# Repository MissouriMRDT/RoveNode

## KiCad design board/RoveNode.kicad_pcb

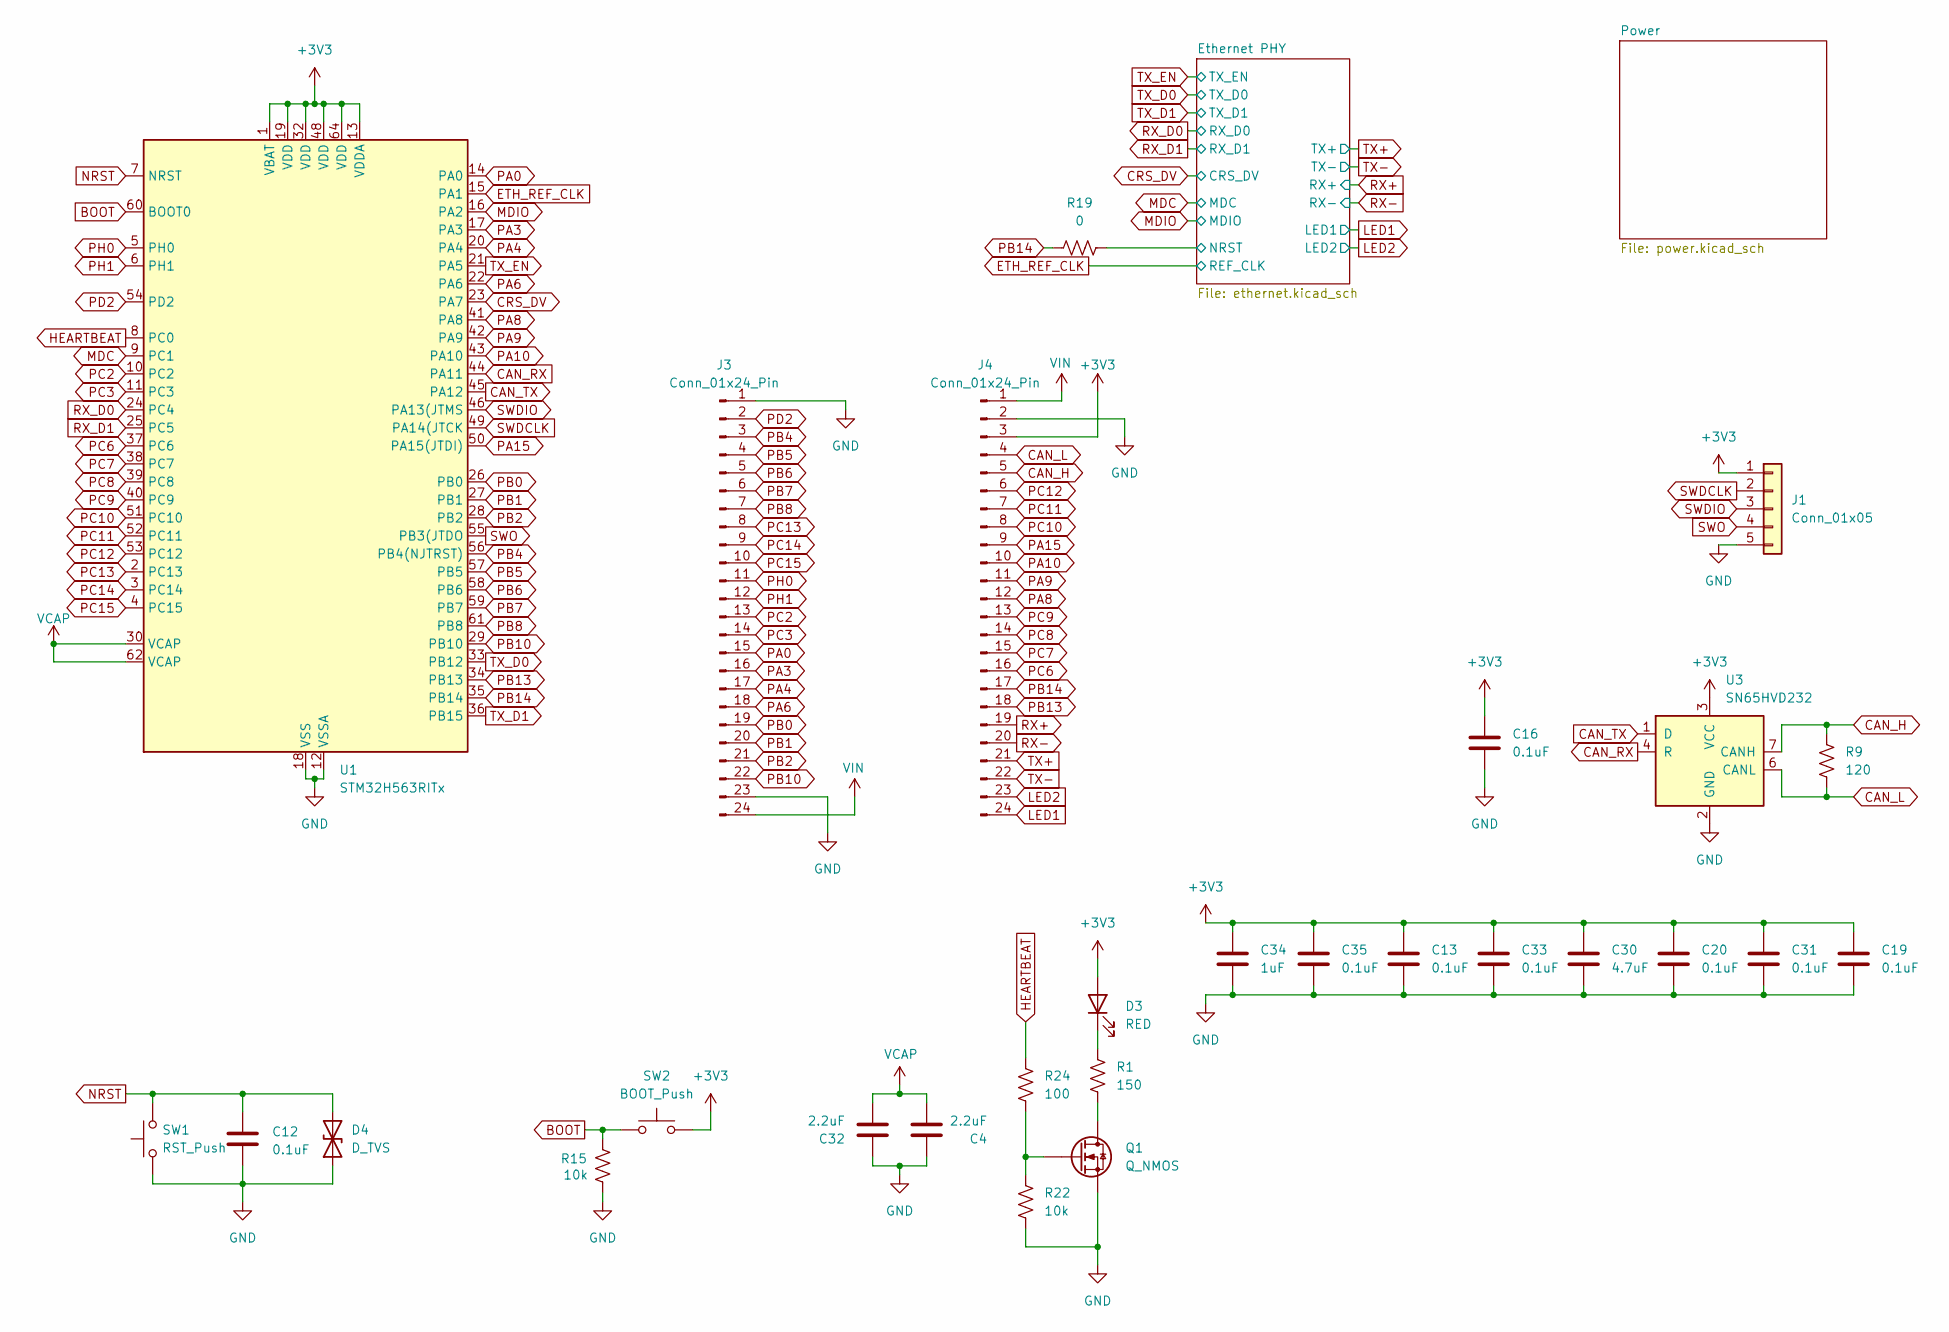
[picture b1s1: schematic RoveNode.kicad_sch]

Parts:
C4, C32: 2.2uF; C_0603_1608Metric_Pad1.08x0.95mm_HandSolder
C12, C13, C16, C19, C20, C31, C33, C35: 0.1uF; C_0603_1608Metric_Pad1.08x0.95mm_HandSolder
C30: 4.7uF; C_0603_1608Metric_Pad1.08x0.95mm_HandSolder
C34: 1uF; C_0603_1608Metric_Pad1.08x0.95mm_HandSolder
D3: RED; LED_0603_1608Metric_Pad1.05x0.95mm_HandSolder
D4: D_TVS; D_0603_1608Metric_Pad1.05x0.95mm_HandSolder
J1: Conn_01x05; JST_PH_S5B-PH-K_1x05_P2.00mm_Horizontal
J3, J4: Conn_01x24_Pin; PinHeader_1x24_P2.54mm_Vertical
Q1: Q_NMOS; SOT-23-3
R1: 150; R_0603_1608Metric_Pad0.98x0.95mm_HandSolder
R9: 120; R_0603_1608Metric_Pad0.98x0.95mm_HandSolder
R15, R22: 10k; R_0603_1608Metric_Pad0.98x0.95mm_HandSolder
R19: 0; R_0603_1608Metric_Pad0.98x0.95mm_HandSolder
R24: 100; R_0603_1608Metric_Pad0.98x0.95mm_HandSolder
SW1: RST_Push; SW_SPST_TL3305A
SW2: BOOT_Push; SW_SPST_TL3305A
U1: STM32H563RITx; LQFP-64_10x10mm_P0.5mm
U3: SN65HVD232; SOIC-8_3.9x4.9mm_P1.27mm

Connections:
+3V3: C13.1, C16.1, C19.1, C20.1, C30.1, C31.1, C33.1, C34.1, C35.1, D3.2 (A), J1.1, J4.3, SW2.2, U1.1 (VBAT), U1.13 (VDDA), U1.19 (VDD), U1.32 (VDD), U1.48 (VDD), U1.64 (VDD), U3.3 (VCC); also elsewhere on the board
/Ethernet PHY/NRST: R19.2; also elsewhere on the board
BOOT: R15.1, SW2.1, U1.60 (BOOT0)
CAN_H: J4.5, R9.1, U3.7 (CANH)
CAN_L: J4.4, R9.2, U3.6 (CANL)
CAN_RX: U1.44 (PA11), U3.4 (R)
CAN_TX: U1.45 (PA12), U3.1 (D)
CRS_DV: U1.23 (PA7); also elsewhere on the board
ETH_REF_CLK: U1.15 (PA1); also elsewhere on the board
GND: C4.1, C12.2, C13.2, C16.2, C19.2, C20.2, C30.2, C31.2, C32.1, C33.2, C34.2, C35.2, D4.1 (A1), J1.5, J3.1, J3.23, J4.2, Q1.1 (S), R15.2, R22.2, SW1.1, U1.12 (VSSA), U1.18 (VSS), U1.31 (VSS), U1.47 (VSS), U1.63 (VSS), U3.2 (GND); also elsewhere on the board
HEARTBEAT: R24.1, U1.8 (PC0)
LED1: J4.24; also elsewhere on the board
LED2: J4.23; also elsewhere on the board
MDC: U1.9 (PC1); also elsewhere on the board
MDIO: U1.16 (PA2); also elsewhere on the board
NRST: C12.1, D4.2 (A2), SW1.2, U1.7 (NRST)
unnamed: D3.1 (K), R1.1
unnamed: Q1.3 (D), R1.2
unnamed: Q1.2 (G), R22.1, R24.2
PA0: J3.15, U1.14 (PA0)
PA3: J3.16, U1.17 (PA3)
PA4: J3.17, U1.20 (PA4)
PA6: J3.18, U1.22 (PA6)
PA8: J4.12, U1.41 (PA8)
PA9: J4.11, U1.42 (PA9)
PA10: J4.10, U1.43 (PA10)
PA15: J4.9, U1.50 (PA15(JTDI))
PB0: J3.19, U1.26 (PB0)
PB1: J3.20, U1.27 (PB1)
PB2: J3.21, U1.28 (PB2)
PB4: J3.3, U1.56 (PB4(NJTRST))
PB5: J3.4, U1.57 (PB5)
PB6: J3.5, U1.58 (PB6)
PB7: J3.6, U1.59 (PB7)
PB8: J3.7, U1.61 (PB8)
PB10: J3.22, U1.29 (PB10)
PB13: J4.18, U1.34 (PB13)
PB14: J4.17, R19.1, U1.35 (PB14)
PC2: J3.13, U1.10 (PC2)
PC3: J3.14, U1.11 (PC3)
PC6: J4.16, U1.37 (PC6)
PC7: J4.15, U1.38 (PC7)
PC8: J4.14, U1.39 (PC8)
PC9: J4.13, U1.40 (PC9)
PC10: J4.8, U1.51 (PC10)
PC11: J4.7, U1.52 (PC11)
PC12: J4.6, U1.53 (PC12)
PC13: J3.8, U1.2 (PC13)
PC14: J3.9, U1.3 (PC14)
PC15: J3.10, U1.4 (PC15)
PD2: J3.2, U1.54 (PD2)
PH0: J3.11, U1.5 (PH0)
PH1: J3.12, U1.6 (PH1)
RX+: J4.19; also elsewhere on the board
RX-: J4.20; also elsewhere on the board
RX_D0: U1.24 (PC4); also elsewhere on the board
RX_D1: U1.25 (PC5); also elsewhere on the board
SWDCLK: J1.2, U1.49 (PA14(JTCK)
SWDIO: J1.3, U1.46 (PA13(JTMS)
SWO: J1.4, U1.55 (PB3(JTDO)
TX+: J4.21; also elsewhere on the board
TX-: J4.22; also elsewhere on the board
TX_D0: U1.33 (PB12); also elsewhere on the board
TX_D1: U1.36 (PB15); also elsewhere on the board
TX_EN: U1.21 (PA5); also elsewhere on the board
VCAP: C4.2, C32.2, U1.30 (VCAP), U1.62 (VCAP)
VIN: J3.24, J4.1; also elsewhere on the board

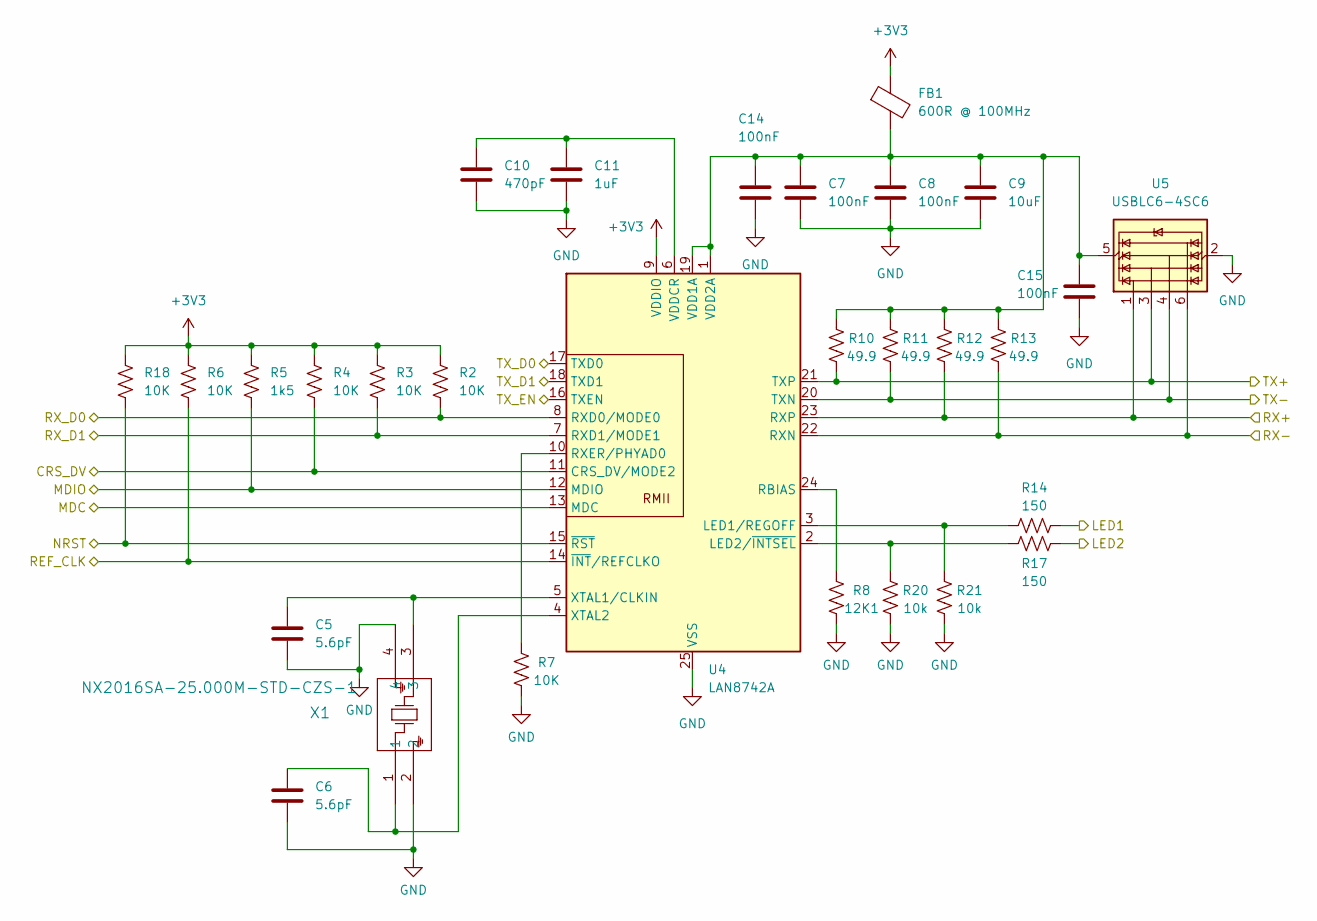
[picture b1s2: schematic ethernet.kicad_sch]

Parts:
C5, C6: 5.6pF; C_0603_1608Metric_Pad1.08x0.95mm_HandSolder
C7, C8, C14, C15: 100nF; C_0603_1608Metric_Pad1.08x0.95mm_HandSolder
C9: 10uF; C_0603_1608Metric_Pad1.08x0.95mm_HandSolder
C10: 470pF; C_0603_1608Metric_Pad1.08x0.95mm_HandSolder
C11: 1uF; C_0603_1608Metric_Pad1.08x0.95mm_HandSolder
FB1: 600R @ 100MHz; IND_HZ0603C601R-10_LRD
R2, R3, R4, R6, R7, R18: 10K; R_0603_1608Metric_Pad0.98x0.95mm_HandSolder
R5: 1k5; R_0603_1608Metric_Pad0.98x0.95mm_HandSolder
R8: 12K1; R_0603_1608Metric_Pad0.98x0.95mm_HandSolder
R10, R11, R12, R13: 49.9; R_0603_1608Metric_Pad0.98x0.95mm_HandSolder
R14, R17: 150; R_0603_1608Metric_Pad0.98x0.95mm_HandSolder
R20, R21: 10k; R_0603_1608Metric_Pad0.98x0.95mm_HandSolder
U4: LAN8742A; VQFN-24-1EP_4x4mm_P0.5mm_EP2.5x2.5mm_ThermalVias
U5: USBLC6-4SC6; SOT-23-6
X1: NX2016SA-25.000M-STD-CZS-1; NX2016SA_NDK

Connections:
+3V3: FB1.1, R2.2, R3.2, R4.2, R5.2, R6.2, R18.2, U4.9 (VDDIO); also elsewhere on the board
/Ethernet PHY/NRST: R18.1, U4.15 (~RST); also elsewhere on the board
CRS_DV: R4.1, U4.11 (CRS_DV/MODE2); also elsewhere on the board
ETH_REF_CLK: R6.1, U4.14 (~INT/REFCLKO); also elsewhere on the board
GND: C5.2, C6.2, C7.2, C8.2, C9.2, C10.2, C11.2, C14.2, C15.2, R7.2, R8.2, R20.2, R21.2, U4.25 (VSS), U5.2 (GND), X1.2, X1.4; also elsewhere on the board
LED1: R14.2; also elsewhere on the board
LED2: R17.2; also elsewhere on the board
MDC: U4.13 (MDC); also elsewhere on the board
MDIO: R5.1, U4.12 (MDIO); also elsewhere on the board
unnamed: R14.1, R21.1, U4.3 (LED1/REGOFF)
unnamed: R17.1, R20.1, U4.2 (LED2/~INTSEL)
unnamed: R8.1, U4.24 (RBIAS)
unnamed: R7.1, U4.10 (RXER/PHYAD0)
unnamed: C7.1, C8.1, C9.1, C14.1, C15.1, FB1.2, R10.1, R11.1, R12.1, R13.1, U4.1 (VDD2A), U4.19 (VDD1A), U5.5 (VBUS)
unnamed: C10.1, C11.1, U4.6 (VDDCR)
unnamed: C5.1, U4.5 (XTAL1/CLKIN), X1.3
unnamed: C6.1, U4.4 (XTAL2), X1.1
RX+: R12.2, U4.23 (RXP), U5.1 (I/O1); also elsewhere on the board
RX-: R13.2, U4.22 (RXN), U5.6 (I/O4); also elsewhere on the board
RX_D0: R2.1, U4.8 (RXD0/MODE0); also elsewhere on the board
RX_D1: R3.1, U4.7 (RXD1/MODE1); also elsewhere on the board
TX+: R10.2, U4.21 (TXP), U5.3 (I/O2); also elsewhere on the board
TX-: R11.2, U4.20 (TXN), U5.4 (I/O3); also elsewhere on the board
TX_D0: U4.17 (TXD0); also elsewhere on the board
TX_D1: U4.18 (TXD1); also elsewhere on the board
TX_EN: U4.16 (TXEN); also elsewhere on the board

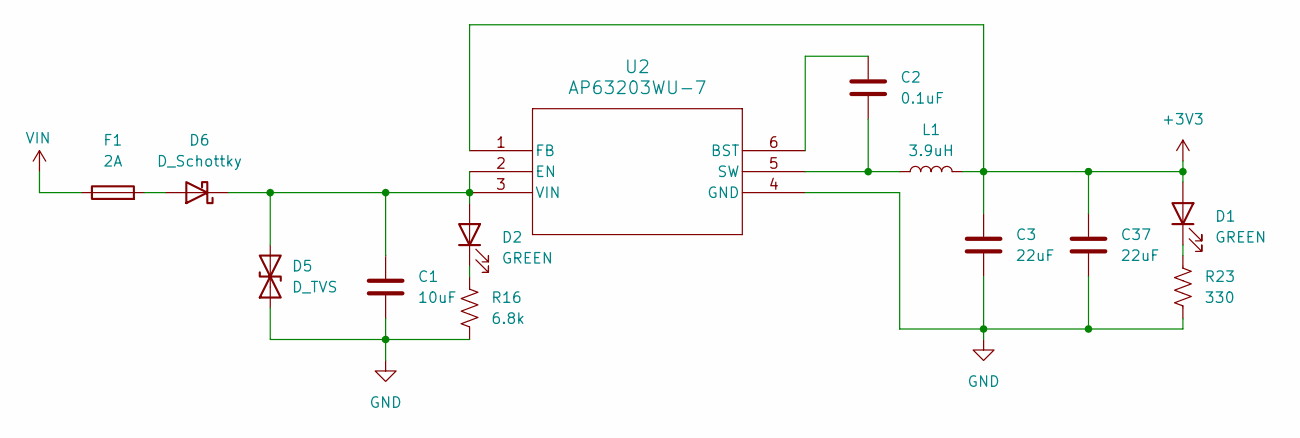
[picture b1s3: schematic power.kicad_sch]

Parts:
C1: 10uF; C_0603_1608Metric_Pad1.08x0.95mm_HandSolder
C2: 0.1uF; C_0603_1608Metric_Pad1.08x0.95mm_HandSolder
C3, C37: 22uF; C_0603_1608Metric_Pad1.08x0.95mm_HandSolder
D1, D2: GREEN; LED_0603_1608Metric_Pad1.05x0.95mm_HandSolder
D5: D_TVS; D_SMA
D6: D_Schottky; D_SOD-123F
F1: 2A; Fuse_1206_3216Metric_Pad1.42x1.75mm_HandSolder
L1: 3.9uH; L_1812_4532Metric_Pad1.30x3.40mm_HandSolder
R16: 6.8k; R_0603_1608Metric_Pad0.98x0.95mm_HandSolder
R23: 330; R_0603_1608Metric_Pad0.98x0.95mm_HandSolder
U2: AP63203WU-7; AP63203WU-7_DIO

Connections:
+3V3: C3.1, C37.1, D1.2 (A), L1.2, U2.1 (FB); also elsewhere on the board
GND: C1.2, C3.2, C37.2, D5.1 (A1), R16.1, R23.1, U2.4 (GND); also elsewhere on the board
unnamed: D1.1 (K), R23.2
unnamed: C1.1, D2.2 (A), D5.2 (A2), D6.1 (K), U2.2 (EN), U2.3 (VIN)
unnamed: D2.1 (K), R16.2
unnamed: D6.2 (A), F1.2
unnamed: C2.1, U2.6 (BST)
unnamed: C2.2, L1.1, U2.5 (SW)
VIN: F1.1; also elsewhere on the board

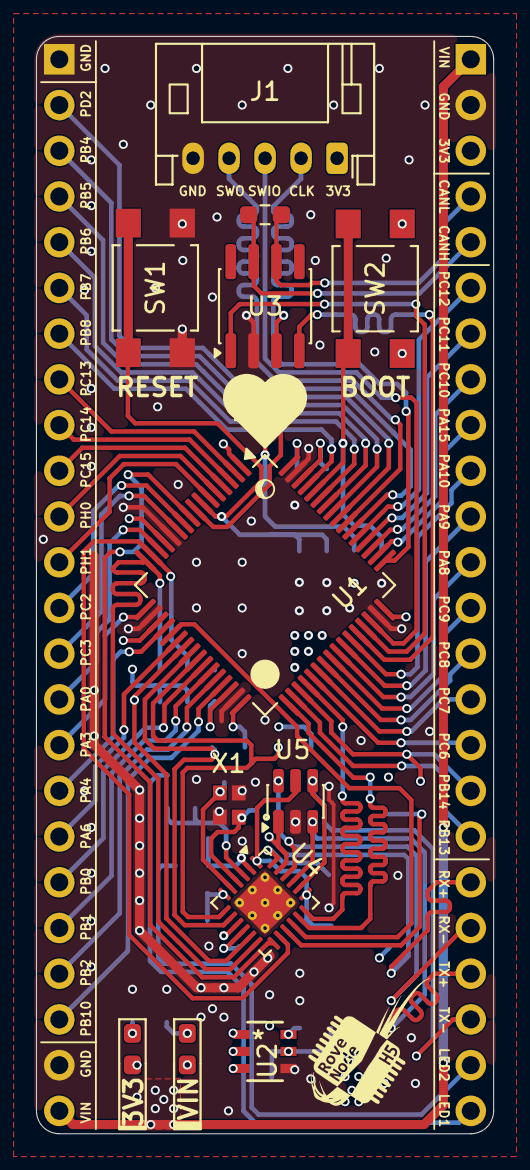
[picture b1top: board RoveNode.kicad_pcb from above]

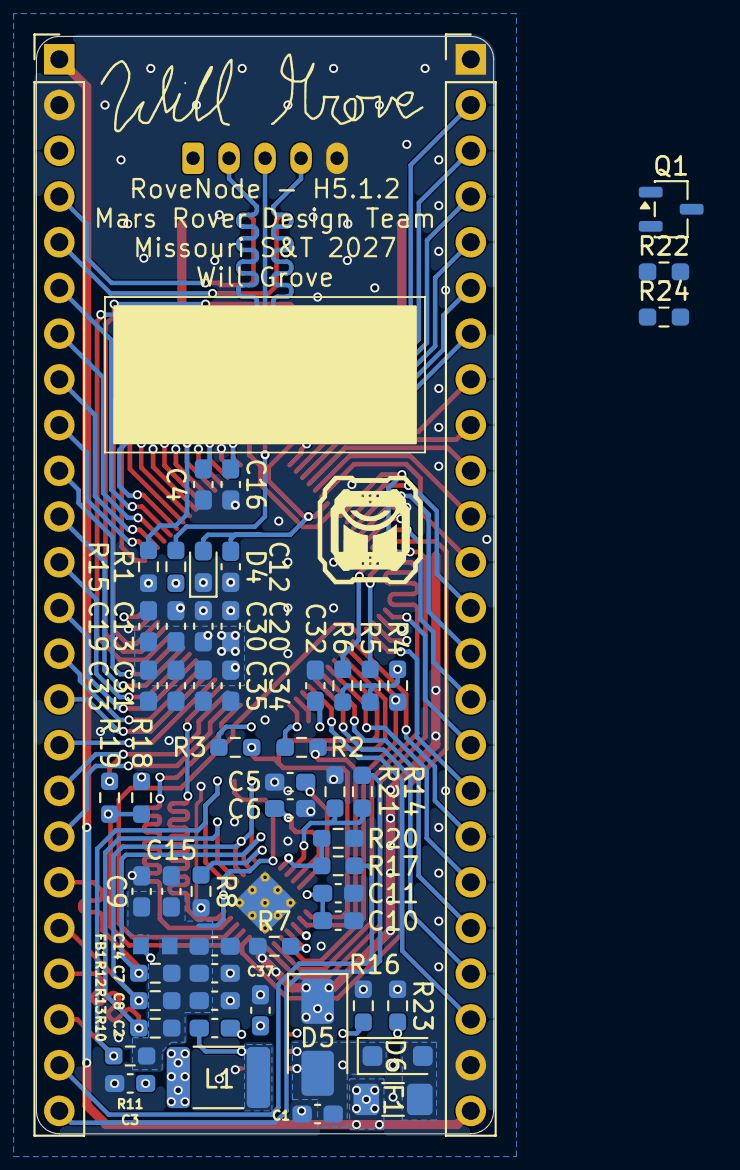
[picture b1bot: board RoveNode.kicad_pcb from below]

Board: 4 copper layers, 25.4 x 61.0 mm, 70 parts (57 on the bottom side), 81 nets.

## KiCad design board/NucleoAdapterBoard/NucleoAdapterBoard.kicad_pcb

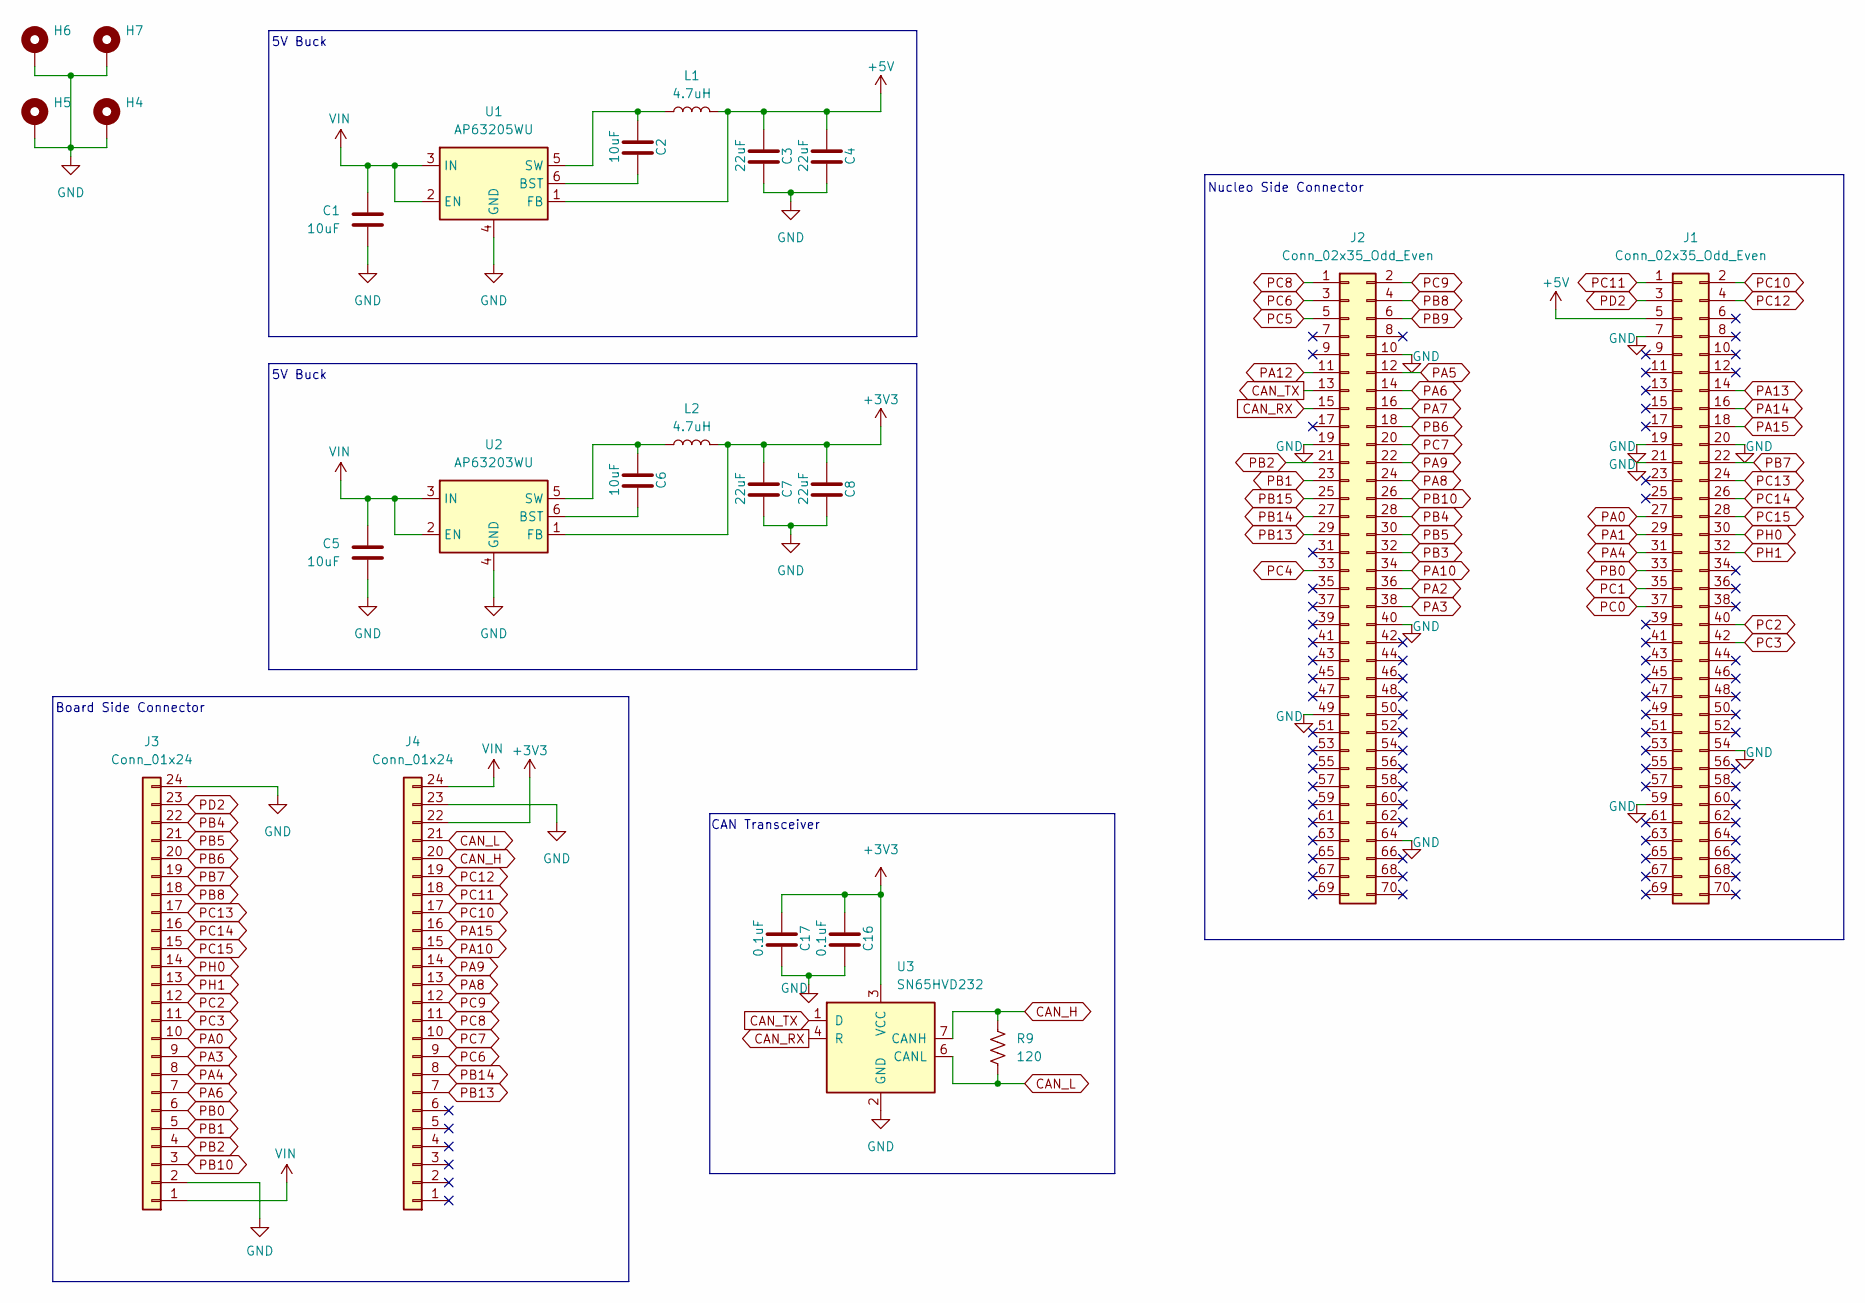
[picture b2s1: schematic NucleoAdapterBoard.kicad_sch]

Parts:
C1, C2, C5, C6: 10uF; C_0603_1608Metric_Pad1.08x0.95mm_HandSolder
C3, C4, C7, C8: 22uF; C_0603_1608Metric_Pad1.08x0.95mm_HandSolder
C16, C17: 0.1uF; C_0603_1608Metric_Pad1.08x0.95mm_HandSolder
H4, H5, H6, H7: MountingHole_Pad; 4_40_Hole_Pad_Via
J1, J2: Conn_02x35_Odd_Even; PinHeader_2x35_P2.54mm_Vertical
J3, J4: Conn_01x24; PinHeader_1x24_P2.54mm_Vertical
L1, L2: 4.7uH; L_Abracon_ASPI-4030S
R9: 120; R_0603_1608Metric_Pad0.98x0.95mm_HandSolder
U1: AP63205WU; TSOT-23-6
U2: AP63203WU; TSOT-23-6
U3: SN65HVD232; SOIC-8_3.9x4.9mm_P1.27mm

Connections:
+3V3: C7.1, C8.1, C16.1, C17.1, J4.22, L2.2, U2.1 (FB), U3.3 (VCC)
+5V: C3.1, C4.1, J1.5, L1.2, U1.1 (FB)
CAN_H: J4.20, R9.1, U3.7 (CANH)
CAN_L: J4.21, R9.2, U3.6 (CANL)
CAN_RX: J2.15, U3.4 (R)
CAN_TX: J2.13, U3.1 (D)
GND: C1.2, C3.2, C4.2, C5.2, C7.2, C8.2, C16.2, C17.2, H4.1 (1_1), H5.1 (1_1), H6.1 (1_1), H7.1 (1_1), J1.7, J1.19, J1.20, J1.21, J1.54, J1.59, J2.10, J2.19, J2.40, J2.49, J2.64, J3.2, J3.24, J4.23, U1.4 (GND), U2.4 (GND), U3.2 (GND)
unnamed: C2.2, U1.6 (BST)
unnamed: C2.1, L1.1, U1.5 (SW)
unnamed: C6.2, U2.6 (BST)
unnamed: C6.1, L2.1, U2.5 (SW)
PA0: J1.27, J3.10
PA1: J1.29
PA2: J2.36
PA3: J2.38, J3.9
PA4: J1.31, J3.8
PA5: J2.12
PA6: J2.14, J3.7
PA7: J2.16
PA8: J2.24, J4.13
PA9: J2.22, J4.14
PA10: J2.34, J4.15
PA12: J2.11
PA13: J1.14
PA14: J1.16
PA15: J1.18, J4.16
PB0: J1.33, J3.6
PB1: J2.23, J3.5
PB2: J2.21, J3.4
PB3: J2.32
PB4: J2.28, J3.22
PB5: J2.30, J3.21
PB6: J2.18, J3.20
PB7: J1.22, J3.19
PB8: J2.4, J3.18
PB9: J2.6
PB10: J2.26, J3.3
PB13: J2.29, J4.7
PB14: J2.27, J4.8
PB15: J2.25
PC0: J1.37
PC1: J1.35
PC2: J1.40, J3.12
PC3: J1.42, J3.11
PC4: J2.33
PC5: J2.5
PC6: J2.3, J4.9
PC7: J2.20, J4.10
PC8: J2.1, J4.11
PC9: J2.2, J4.12
PC10: J1.2, J4.17
PC11: J1.1, J4.18
PC12: J1.4, J4.19
PC13: J1.24, J3.17
PC14: J1.26, J3.16
PC15: J1.28, J3.15
PD2: J1.3, J3.23
PH0: J1.30, J3.14
PH1: J1.32, J3.13
VIN: C1.1, C5.1, J3.1, J4.24, U1.2 (EN), U1.3 (IN), U2.2 (EN), U2.3 (IN)

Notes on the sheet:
5V Buck
CAN Transceiver
Board Side Connector
Nucleo Side Connector

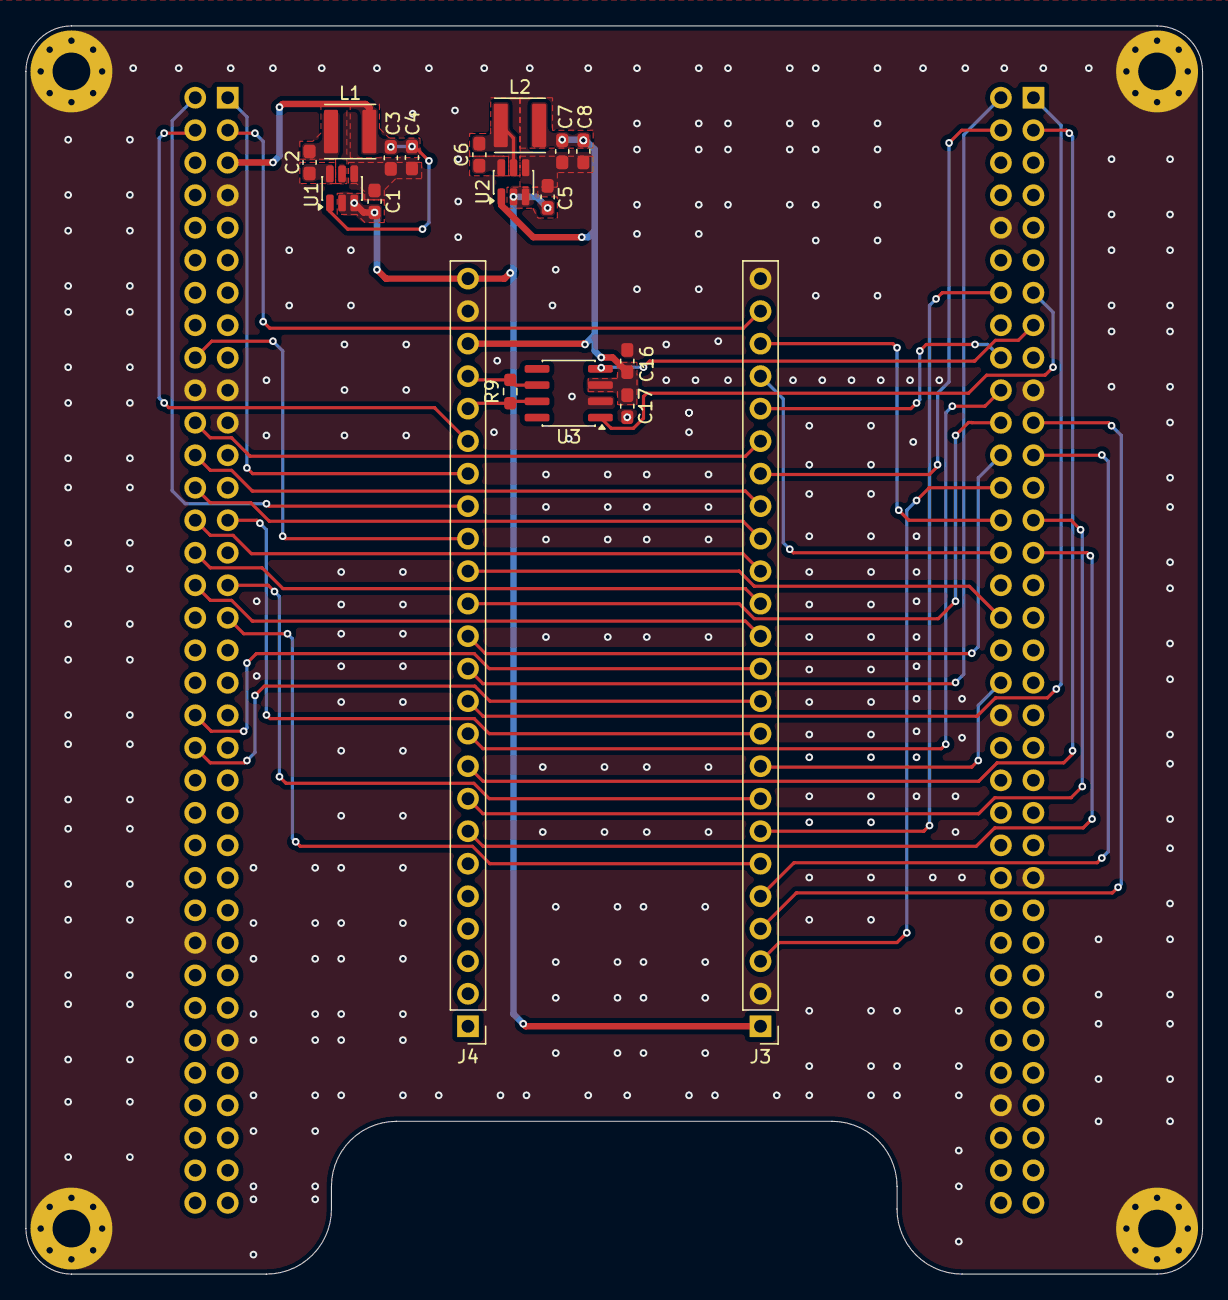
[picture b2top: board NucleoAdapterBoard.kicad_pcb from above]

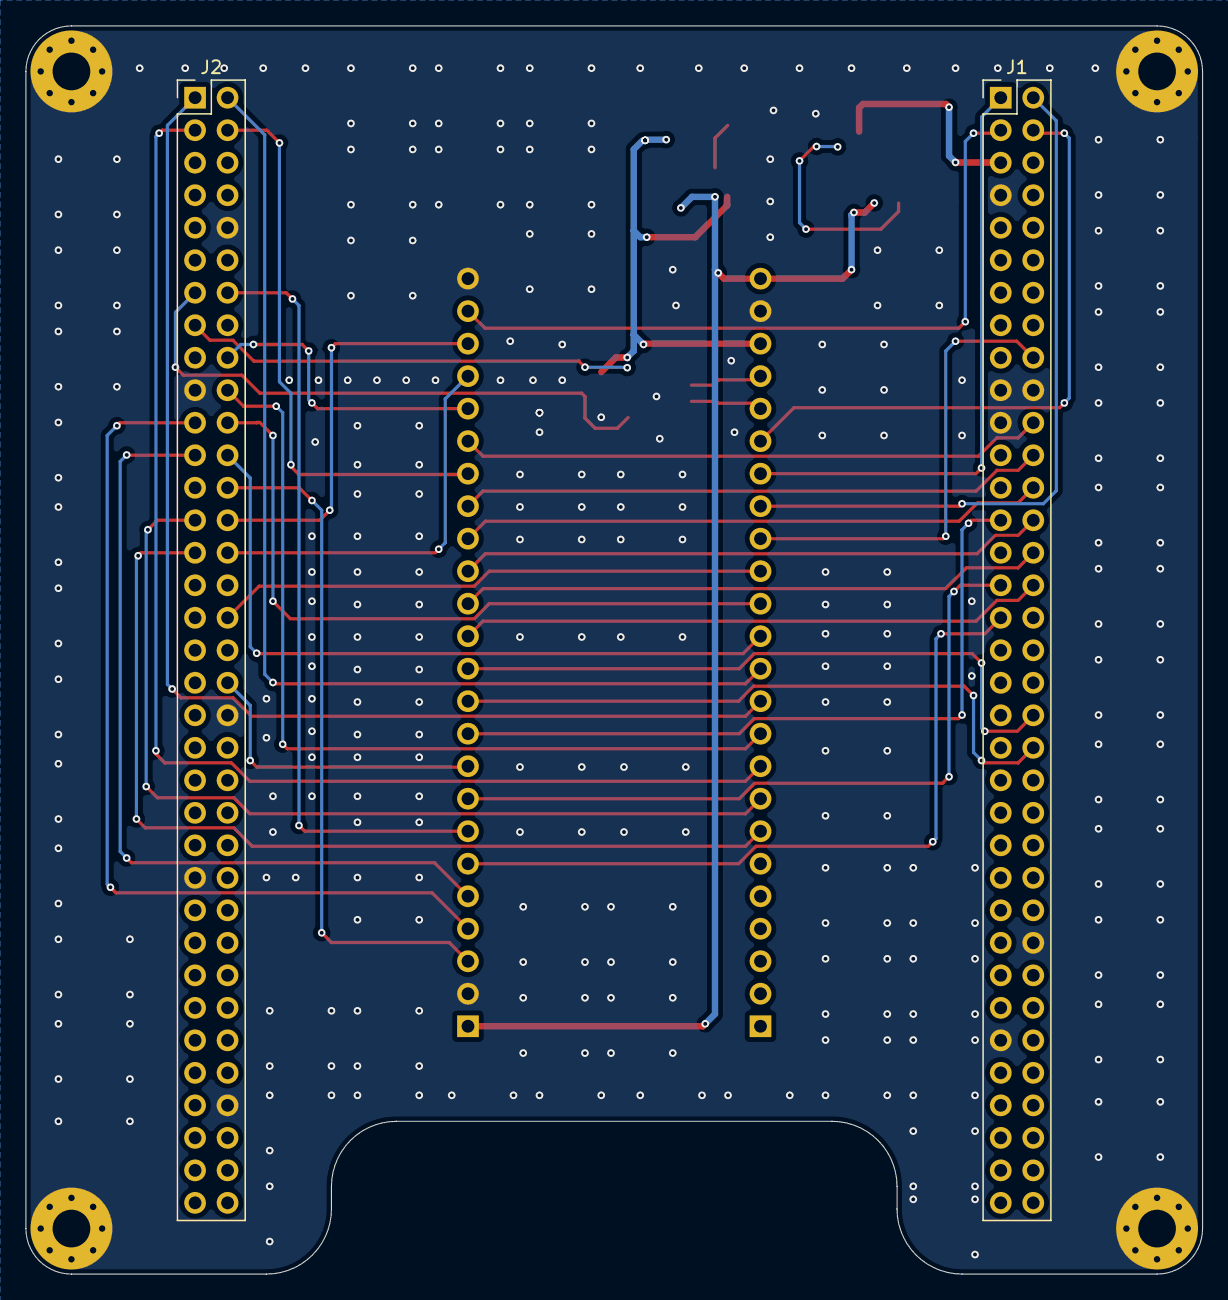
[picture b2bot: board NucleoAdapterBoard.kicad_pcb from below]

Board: 2 copper layers, 91.9 x 97.5 mm, 24 parts (2 on the bottom side), 46 nets.
